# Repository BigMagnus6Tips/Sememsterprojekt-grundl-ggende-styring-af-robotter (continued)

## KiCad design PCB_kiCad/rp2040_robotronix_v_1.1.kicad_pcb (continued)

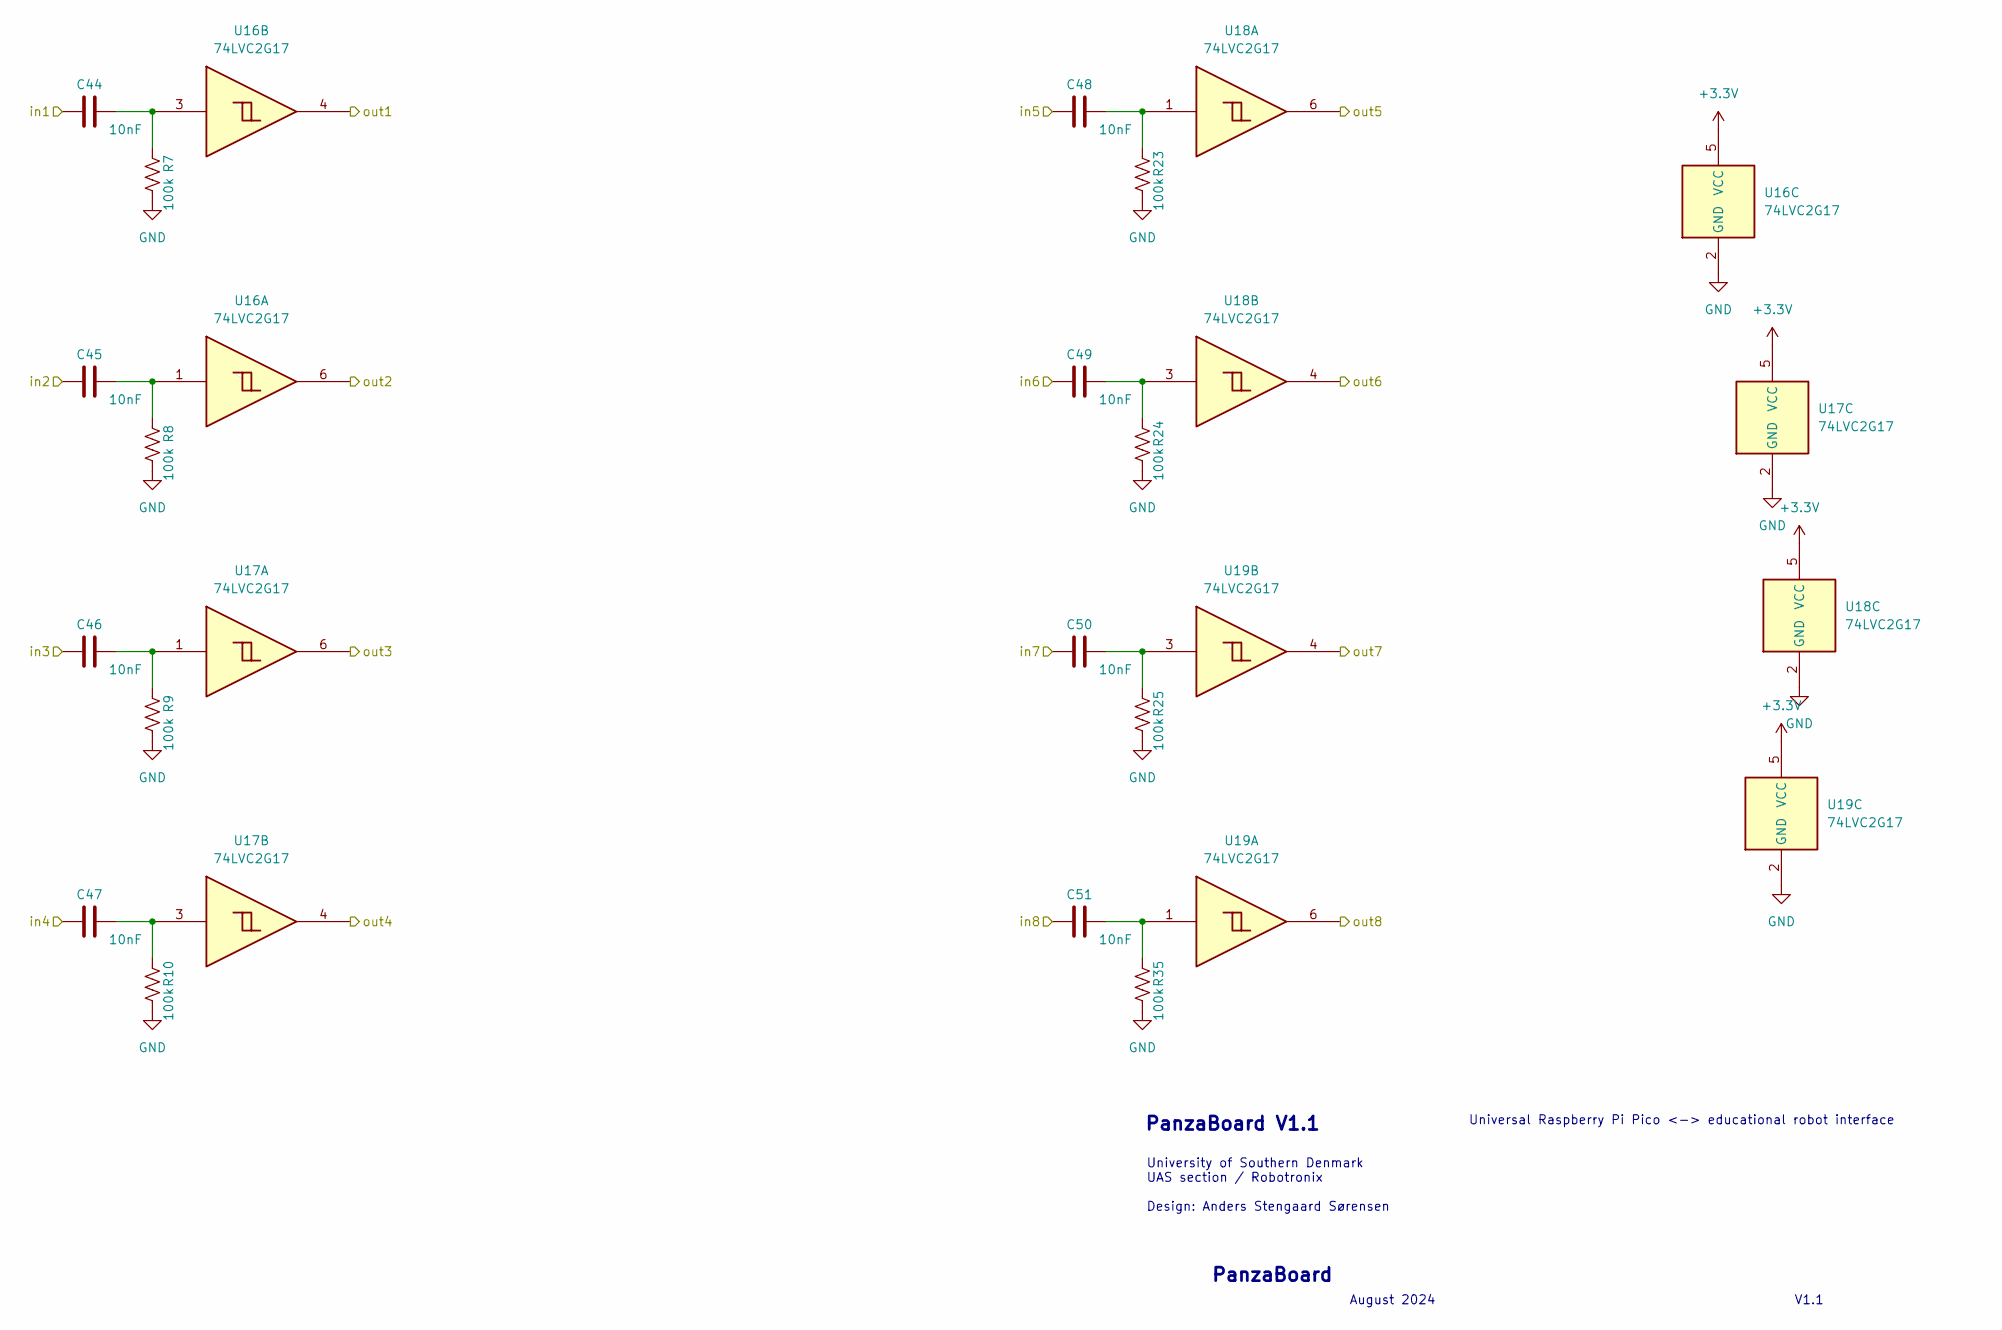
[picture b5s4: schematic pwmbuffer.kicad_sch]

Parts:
C44, C45, C46, C47, C48, C49, C50, C51: 10nF; C_0603_1608Metric
R7, R8, R9, R10, R23, R24, R25, R35: 100k; R_0603_1608Metric
U16, U17, U18, U19: 74LVC2G17; TSOP-6_1.65x3.05mm_P0.95mm

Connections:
/GP0: C44.2; also elsewhere on the board
/GP1: C45.2; also elsewhere on the board
/GP2: C46.2; also elsewhere on the board
/GP3: C47.2; also elsewhere on the board
/GP4: C48.2; also elsewhere on the board
/GP5: C49.2; also elsewhere on the board
/GP6: C50.2; also elsewhere on the board
/GP7: C51.2; also elsewhere on the board
/Motor drivers/PWM1: U16.4; also elsewhere on the board
/Motor drivers/PWM2: U16.6; also elsewhere on the board
/Motor drivers/PWM3: U17.6; also elsewhere on the board
/Motor drivers/PWM4: U17.4; also elsewhere on the board
/Motor drivers/PWM5: U18.6; also elsewhere on the board
/Motor drivers/PWM6: U18.4; also elsewhere on the board
/Motor drivers/PWM7: U19.4; also elsewhere on the board
/Motor drivers/PWM8: U19.6; also elsewhere on the board
GND: R7.2, R8.2, R9.2, R10.2, R23.2, R24.2, R25.2, R35.2, U16.2 (GND), U17.2 (GND), U18.2 (GND), U19.2 (GND); also elsewhere on the board
unnamed: C44.1, R7.1, U16.3
unnamed: C45.1, R8.1, U16.1
unnamed: C46.1, R9.1, U17.1
unnamed: C47.1, R10.1, U17.3
unnamed: C48.1, R23.1, U18.1
unnamed: C49.1, R24.1, U18.3
unnamed: C50.1, R25.1, U19.3
unnamed: C51.1, R35.1, U19.1
SD: U16.5 (VCC), U17.5 (VCC), U18.5 (VCC), U19.5 (VCC); also elsewhere on the board

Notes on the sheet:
Universal Raspberry Pi Pico <-> educational robot interface
August 2024
PanzaBoard V1.1
University of Southern Denmark UAS section / Robotronix Design: Anders Stengaard Sørensen
V1.1
PanzaBoard

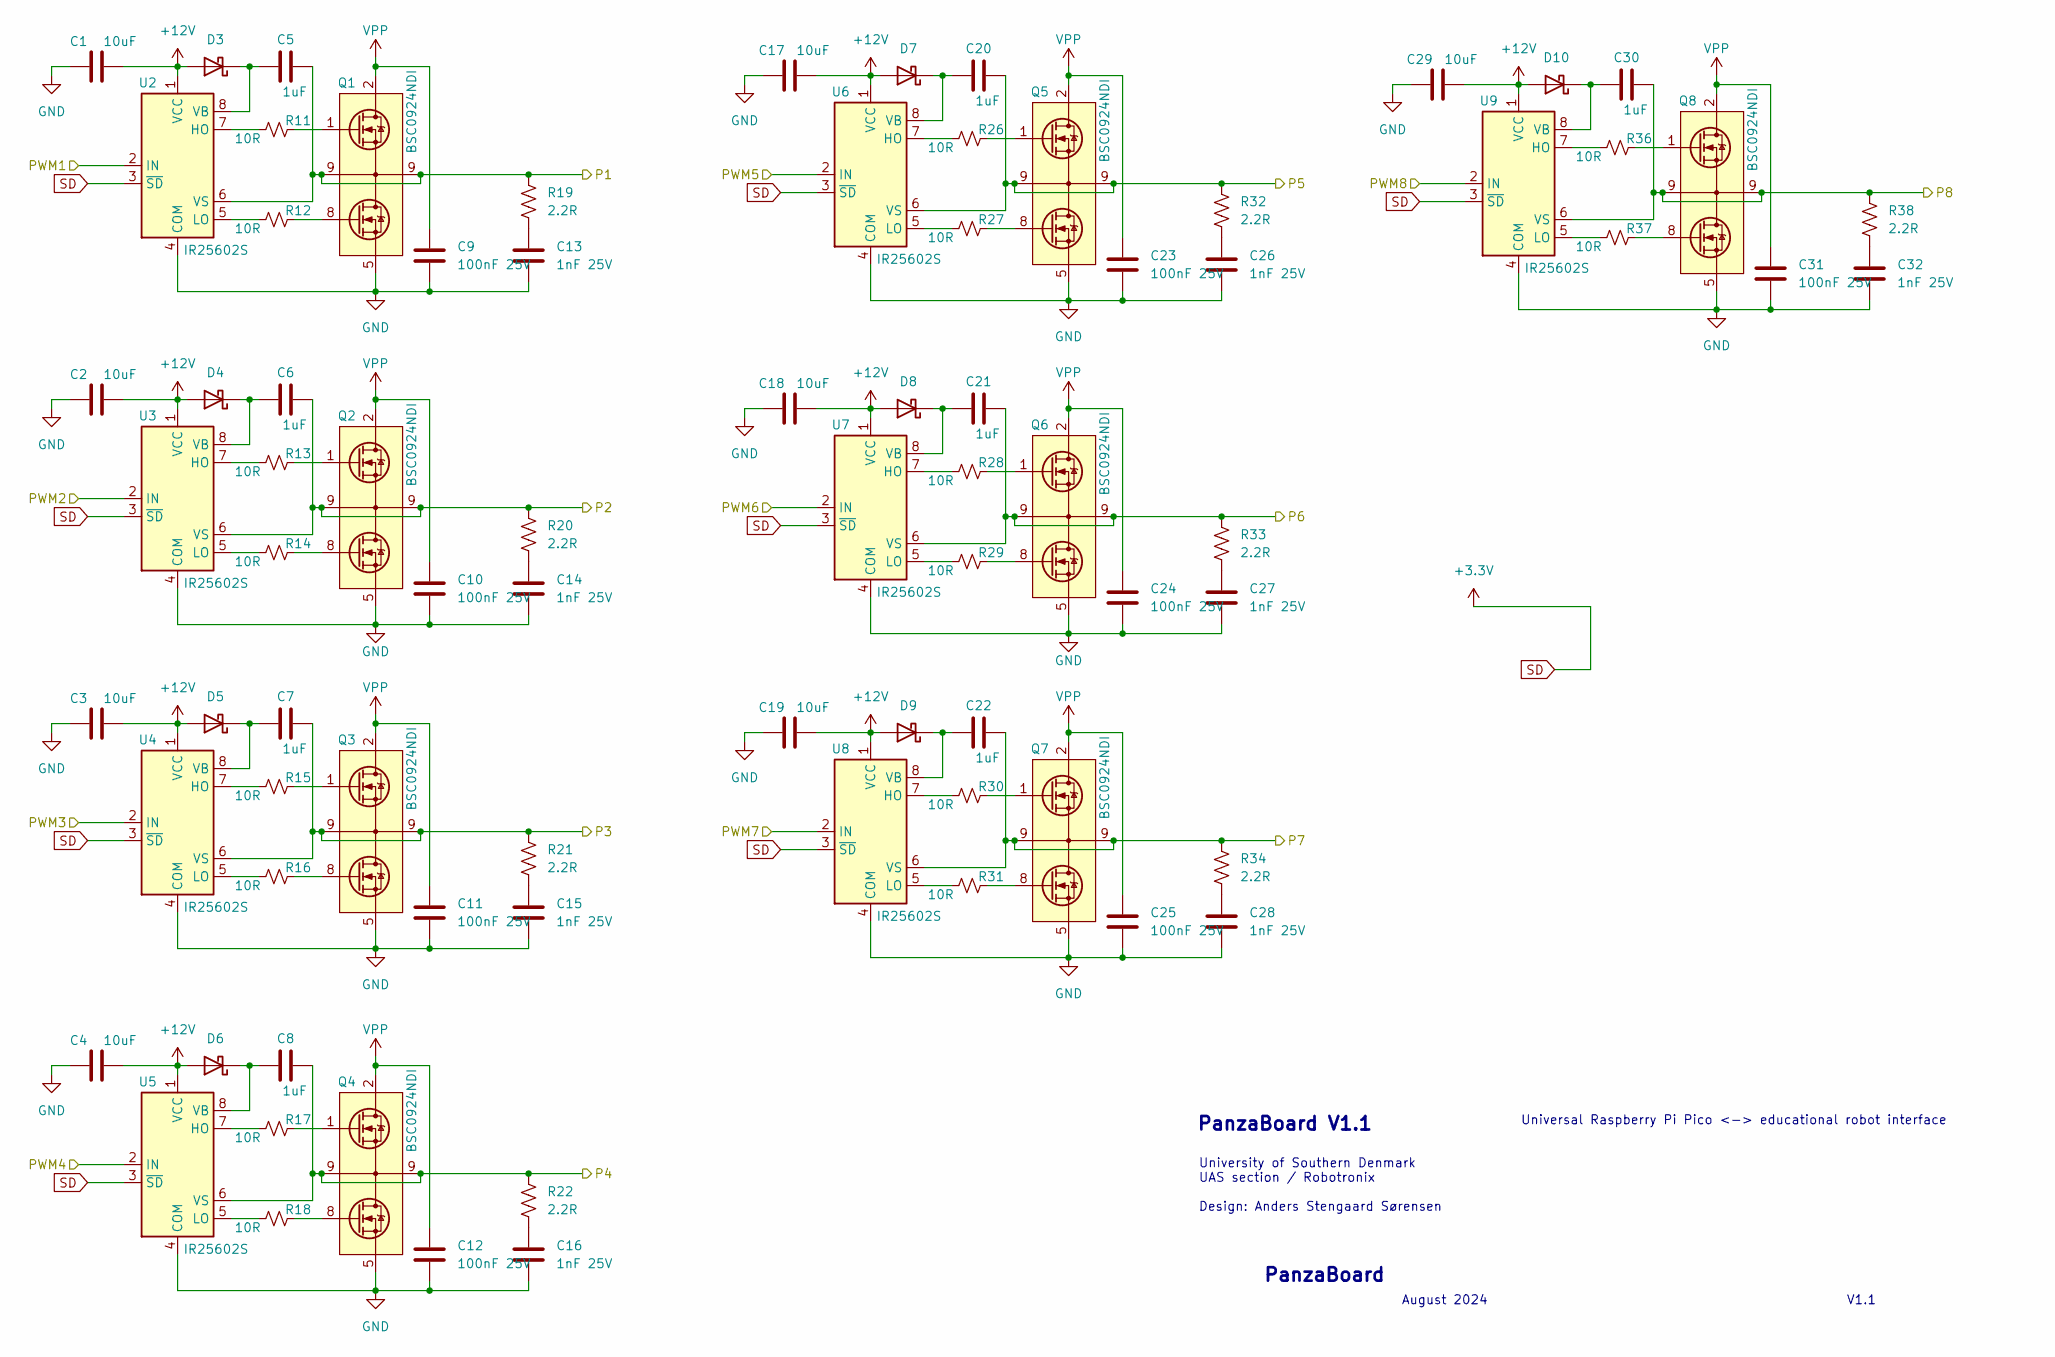
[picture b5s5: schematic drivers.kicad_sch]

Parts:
C1, C2, C3, C4, C17, C18, C19, C29: 10uF; C_1206_3216Metric; MFR# CL31A106KAHNFNE
C5, C6, C7, C8, C20, C21, C22, C30: 1uF; C_0603_1608Metric
C9, C10, C11, C12, C23, C24, C25, C31: 100nF 25V; C_0603_1608Metric
C13, C14, C15, C16, C26, C27, C28, C32: 1nF 25V; C_0603_1608Metric
D3, D4, D5, D6, D7, D8, D9, D10: CES521; D_SOD-523
Q1, Q2, Q3, Q4, Q5, Q6, Q7, Q8: BSC0924NDI; PG-TISON8; MFR# Infineon Technologies
R11, R12, R13, R14, R15, R16, R17, R18, R26, R27, R28, R29, R30, R31, R36, R37: 10R; R_0603_1608Metric
R19, R20, R21, R22, R32, R33, R34, R38: 2.2R; R_0603_1608Metric
U2, U3, U4, U5, U6, U7, U8, U9: IR25602S; SOIC-8_3.9x4.9mm_P1.27mm

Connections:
+12V: C1.2, C2.2, C3.2, C4.2, C17.2, C18.2, C19.2, C29.2, D3.2 (A), D4.2 (A), D5.2 (A), D6.2 (A), D7.2 (A), D8.2 (A), D9.2 (A), D10.2 (A), U2.1 (VCC), U3.1 (VCC), U4.1 (VCC), U5.1 (VCC), U6.1 (VCC), U7.1 (VCC), U8.1 (VCC), U9.1 (VCC); also elsewhere on the board
/Motor drivers/P1: C5.2, Q1.9, R19.1, U2.6 (VS); also elsewhere on the board
/Motor drivers/P2: C6.2, Q2.9, R20.1, U3.6 (VS); also elsewhere on the board
/Motor drivers/P3: C7.2, Q3.9, R21.1, U4.6 (VS); also elsewhere on the board
/Motor drivers/P4: C8.2, Q4.9, R22.1, U5.6 (VS); also elsewhere on the board
/Motor drivers/P5: C20.2, Q5.9, R32.1, U6.6 (VS); also elsewhere on the board
/Motor drivers/P6: C21.2, Q6.9, R33.1, U7.6 (VS); also elsewhere on the board
/Motor drivers/P7: C22.2, Q7.9, R34.1, U8.6 (VS); also elsewhere on the board
/Motor drivers/P8: C30.2, Q8.9, R38.1, U9.6 (VS); also elsewhere on the board
/Motor drivers/PWM1: U2.2 (IN); also elsewhere on the board
/Motor drivers/PWM2: U3.2 (IN); also elsewhere on the board
/Motor drivers/PWM3: U4.2 (IN); also elsewhere on the board
/Motor drivers/PWM4: U5.2 (IN); also elsewhere on the board
/Motor drivers/PWM5: U6.2 (IN); also elsewhere on the board
/Motor drivers/PWM6: U7.2 (IN); also elsewhere on the board
/Motor drivers/PWM7: U8.2 (IN); also elsewhere on the board
/Motor drivers/PWM8: U9.2 (IN); also elsewhere on the board
GND: C1.1, C2.1, C3.1, C4.1, C9.1, C10.1, C11.1, C12.1, C13.1, C14.1, C15.1, C16.1, C17.1, C18.1, C19.1, C23.1, C24.1, C25.1, C26.1, C27.1, C28.1, C29.1, C31.1, C32.1, Q1.5, Q1.6, Q1.7, Q2.5, Q2.6, Q2.7, Q3.5, Q3.6, Q3.7, Q4.5, Q4.6, Q4.7, Q5.5, Q5.6, Q5.7, Q6.5, Q6.6, Q6.7, Q7.5, Q7.6, Q7.7, Q8.5, Q8.6, Q8.7, U2.4 (COM), U3.4 (COM), U4.4 (COM), U5.4 (COM), U6.4 (COM), U7.4 (COM), U8.4 (COM), U9.4 (COM); also elsewhere on the board
unnamed: C13.2, R19.2
unnamed: C14.2, R20.2
unnamed: C15.2, R21.2
unnamed: C16.2, R22.2
unnamed: C26.2, R32.2
unnamed: C27.2, R33.2
unnamed: C28.2, R34.2
unnamed: C32.2, R38.2
unnamed: C5.1, D3.1 (K), U2.8 (VB)
unnamed: C6.1, D4.1 (K), U3.8 (VB)
unnamed: C7.1, D5.1 (K), U4.8 (VB)
unnamed: C8.1, D6.1 (K), U5.8 (VB)
unnamed: C20.1, D7.1 (K), U6.8 (VB)
unnamed: C21.1, D8.1 (K), U7.8 (VB)
unnamed: C22.1, D9.1 (K), U8.8 (VB)
unnamed: C30.1, D10.1 (K), U9.8 (VB)
unnamed: Q1.1, R11.2
unnamed: Q1.8, R12.2
unnamed: Q2.1, R13.2
unnamed: Q2.8, R14.2
unnamed: Q3.1, R15.2
unnamed: Q3.8, R16.2
unnamed: Q4.1, R17.2
unnamed: Q4.8, R18.2
unnamed: Q5.1, R26.2
unnamed: Q5.8, R27.2
unnamed: Q6.1, R28.2
unnamed: Q6.8, R29.2
unnamed: Q7.1, R30.2
unnamed: Q7.8, R31.2
unnamed: Q8.1, R36.2
unnamed: Q8.8, R37.2
unnamed: R11.1, U2.7 (HO)
unnamed: R12.1, U2.5 (LO)
unnamed: R13.1, U3.7 (HO)
unnamed: R14.1, U3.5 (LO)
unnamed: R15.1, U4.7 (HO)
unnamed: R16.1, U4.5 (LO)
unnamed: R17.1, U5.7 (HO)
unnamed: R18.1, U5.5 (LO)
unnamed: R26.1, U6.7 (HO)
unnamed: R27.1, U6.5 (LO)
unnamed: R28.1, U7.7 (HO)
unnamed: R29.1, U7.5 (LO)
unnamed: R30.1, U8.7 (HO)
unnamed: R31.1, U8.5 (LO)
unnamed: R36.1, U9.7 (HO)
unnamed: R37.1, U9.5 (LO)
SD: U2.3 (~SD), U3.3 (~SD), U4.3 (~SD), U5.3 (~SD), U6.3 (~SD), U7.3 (~SD), U8.3 (~SD), U9.3 (~SD); also elsewhere on the board
VPP: C9.2, C10.2, C11.2, C12.2, C23.2, C24.2, C25.2, C31.2, Q1.2, Q1.3, Q1.4, Q2.2, Q2.3, Q2.4, Q3.2, Q3.3, Q3.4, Q4.2, Q4.3, Q4.4, Q5.2, Q5.3, Q5.4, Q6.2, Q6.3, Q6.4, Q7.2, Q7.3, Q7.4, Q8.2, Q8.3, Q8.4; also elsewhere on the board

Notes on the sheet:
PanzaBoard
University of Southern Denmark UAS section / Robotronix Design: Anders Stengaard Sørensen
V1.1
August 2024
Universal Raspberry Pi Pico <-> educational robot interface
PanzaBoard V1.1

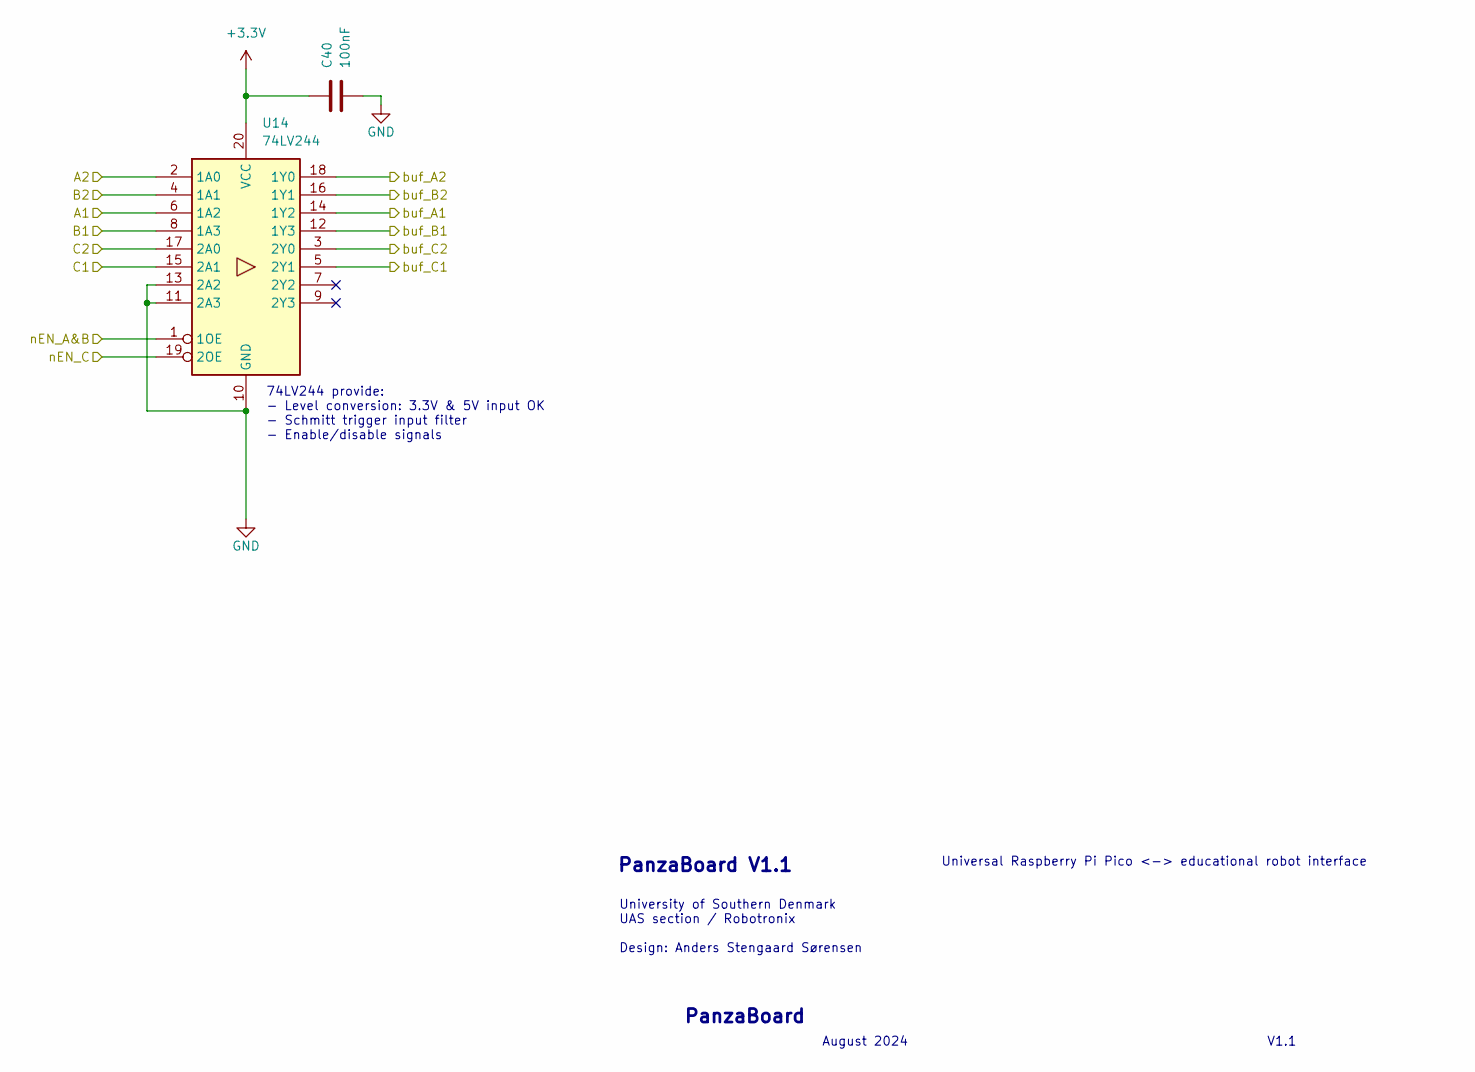
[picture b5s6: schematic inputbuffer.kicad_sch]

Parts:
C40: 100nF; C_0603_1608Metric
U14: 74LV244; TSSOP-20_4.4x6.5mm_P0.65mm; MFR# Nexperia

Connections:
/GP8: U14.5 (2Y1); also elsewhere on the board
/GP9: U14.3 (2Y0); also elsewhere on the board
/GP12: U14.12 (1Y3); also elsewhere on the board
/GP13: U14.14 (1Y2); also elsewhere on the board
/GP14: U14.16 (1Y1); also elsewhere on the board
/GP15: U14.18 (1Y0); also elsewhere on the board
/Input buffer/A1: U14.6 (1A2); also elsewhere on the board
/Input buffer/A2: U14.2 (1A0); also elsewhere on the board
/Input buffer/B1: U14.8 (1A3); also elsewhere on the board
/Input buffer/B2: U14.4 (1A1); also elsewhere on the board
/Input buffer/C1: U14.15 (2A1); also elsewhere on the board
/Input buffer/C2: U14.17 (2A0); also elsewhere on the board
/Input buffer/nEN_A&B: U14.1 (1OE); also elsewhere on the board
/Input buffer/nEN_C: U14.19 (2OE); also elsewhere on the board
GND: C40.1, U14.10 (GND), U14.11 (2A3), U14.13 (2A2); also elsewhere on the board
SD: C40.2, U14.20 (VCC); also elsewhere on the board

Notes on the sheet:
University of Southern Denmark UAS section / Robotronix Design: Anders Stengaard Sørensen
PanzaBoard V1.1
Universal Raspberry Pi Pico <-> educational robot interface
74LV244 provide: - Level conversion: 3.3V & 5V input OK - Schmitt trigger input filter - Enable/disable signals
August 2024
V1.1
PanzaBoard

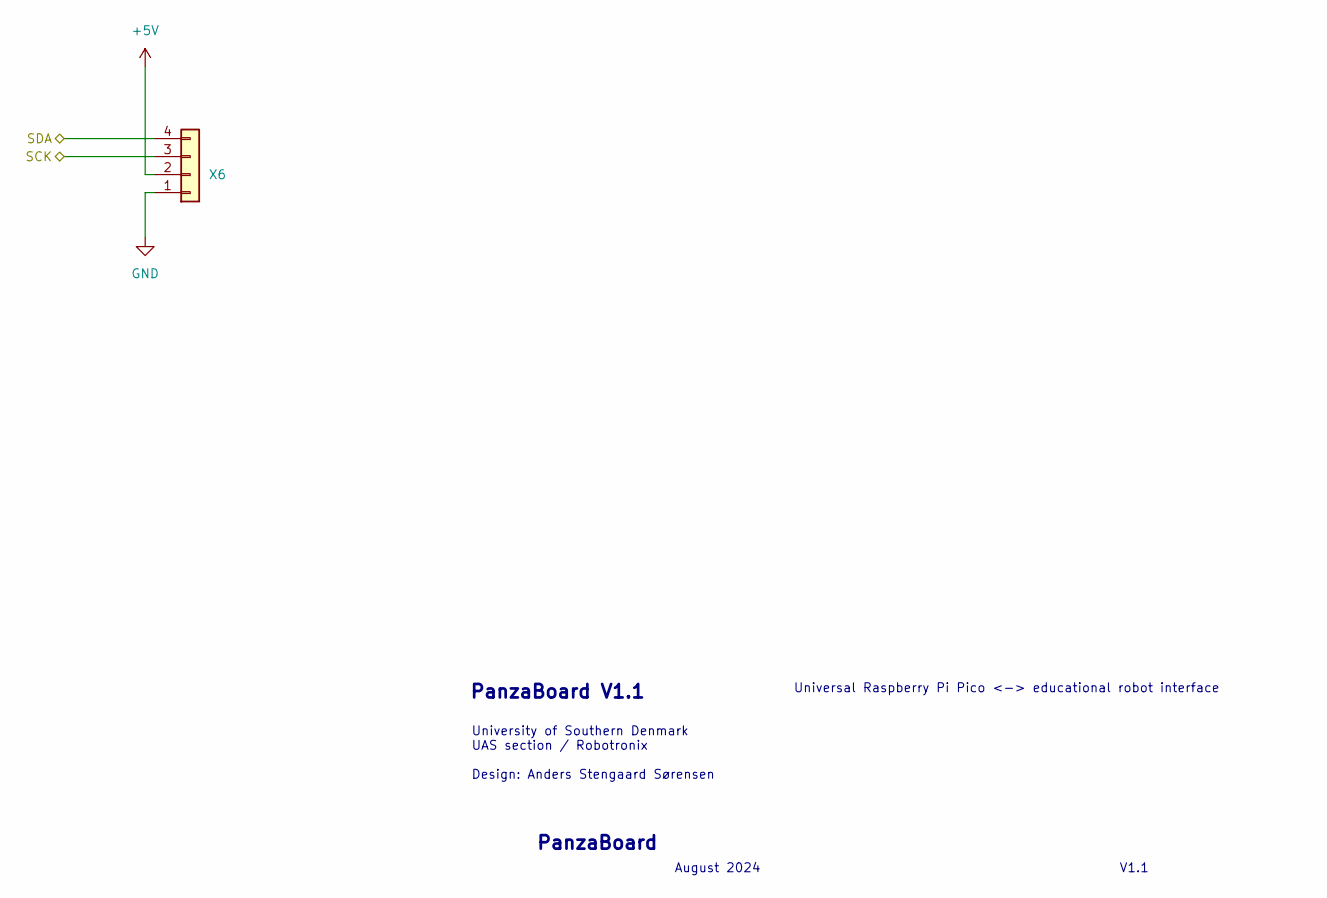
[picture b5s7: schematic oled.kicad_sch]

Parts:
X6: Conn_01x04; Molex_KK-254_AE-6410-04A_1x04_P2.54mm_Vertical

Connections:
+5V: X6.2; also elsewhere on the board
/GP20: X6.4; also elsewhere on the board
/GP21: X6.3; also elsewhere on the board
GND: X6.1; also elsewhere on the board

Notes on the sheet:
Universal Raspberry Pi Pico <-> educational robot interface
PanzaBoard V1.1
August 2024
PanzaBoard
V1.1
University of Southern Denmark UAS section / Robotronix Design: Anders Stengaard Sørensen

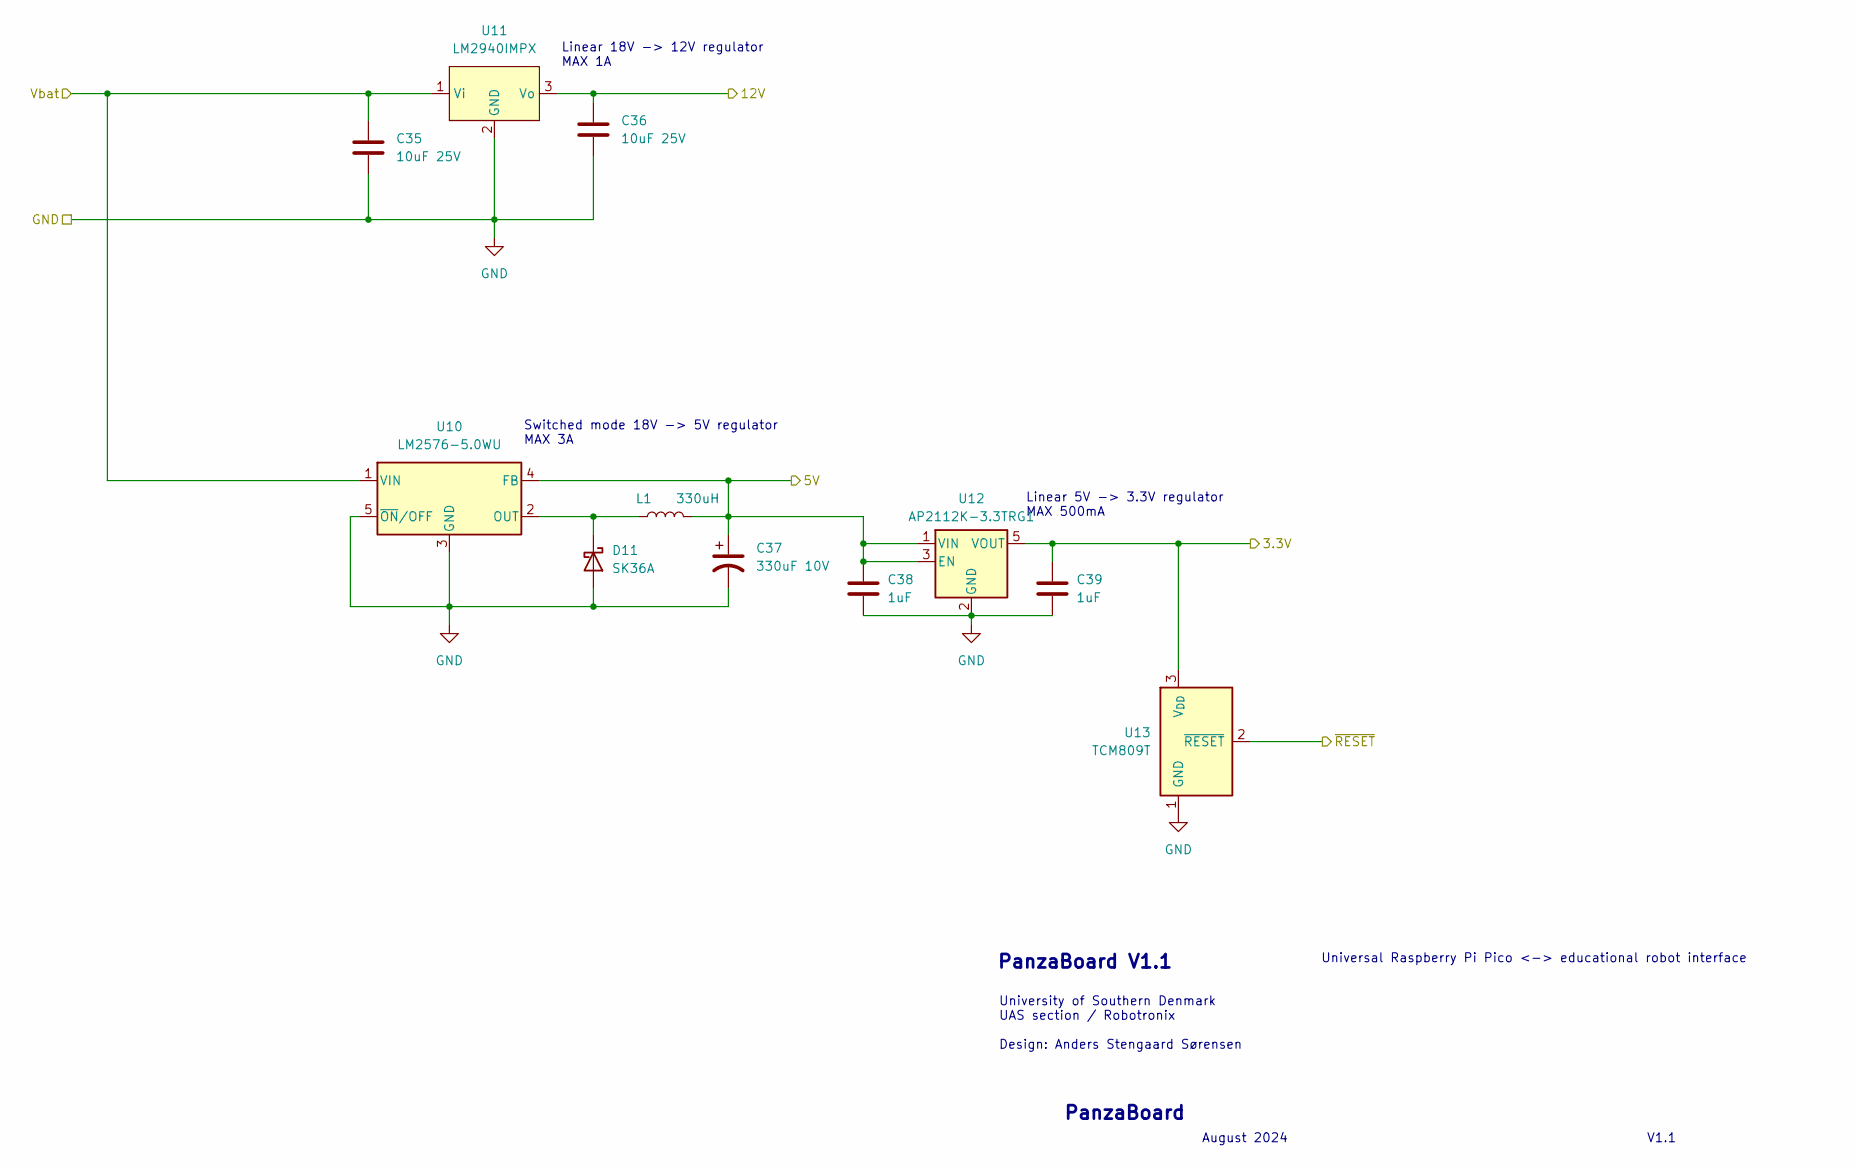
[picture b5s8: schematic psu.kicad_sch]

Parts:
C35, C36: 10uF 25V; C_1206_3216Metric; MFR# CL31A106KAHNFNE
C37: 330uF 10V; CP_Radial_D10.0mm_P5.00mm; MFR# Wurth Elektronik
C38, C39: 1uF; C_1206_3216Metric; MFR# CC0603KPX5R8BB105
D11: SK36A; D_SMA; MFR# Micro Commercial Components (MCC)
L1: 330uH; L_Murata_6000B; MFR# Murata Power Solutions
U10: LM2576-5.0WU; TO-263-5_TabPin3; MFR# Microchip Technology
U11: LM2940IMPX; SOT-223-3_TabPin2
U12: AP2112K-3.3TRG1; SOT-23-5; MFR# Diodes Incorporated
U13: TCM809T; SOT-323_SC-70; MFR# Microchip Technology

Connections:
+5V: C37.1, C38.1, L1.2, U10.4 (FB), U12.1 (VIN), U12.3 (EN); also elsewhere on the board
+12V: C36.1, U11.3 (Vo); also elsewhere on the board
/RUN: U13.2 (~RESET); also elsewhere on the board
GND: C35.2, C36.2, C37.2, C38.2, C39.2, D11.2 (A), U10.3 (GND), U10.5 (~ON/OFF), U11.2 (GND), U12.2 (GND), U13.1 (GND); also elsewhere on the board
unnamed: D11.1 (K), L1.1, U10.2 (OUT)
SD: C39.1, U12.5 (VOUT), U13.3 (V_{DD}); also elsewhere on the board
Vbat: C35.1, U10.1 (VIN), U11.1 (Vi); also elsewhere on the board

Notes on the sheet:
Linear 5V -> 3.3V regulator MAX 500mA
August 2024
University of Southern Denmark UAS section / Robotronix Design: Anders Stengaard Sørensen
Universal Raspberry Pi Pico <-> educational robot interface
Linear 18V -> 12V regulator MAX 1A
PanzaBoard V1.1
Switched mode 18V -> 5V regulator MAX 3A
PanzaBoard
V1.1

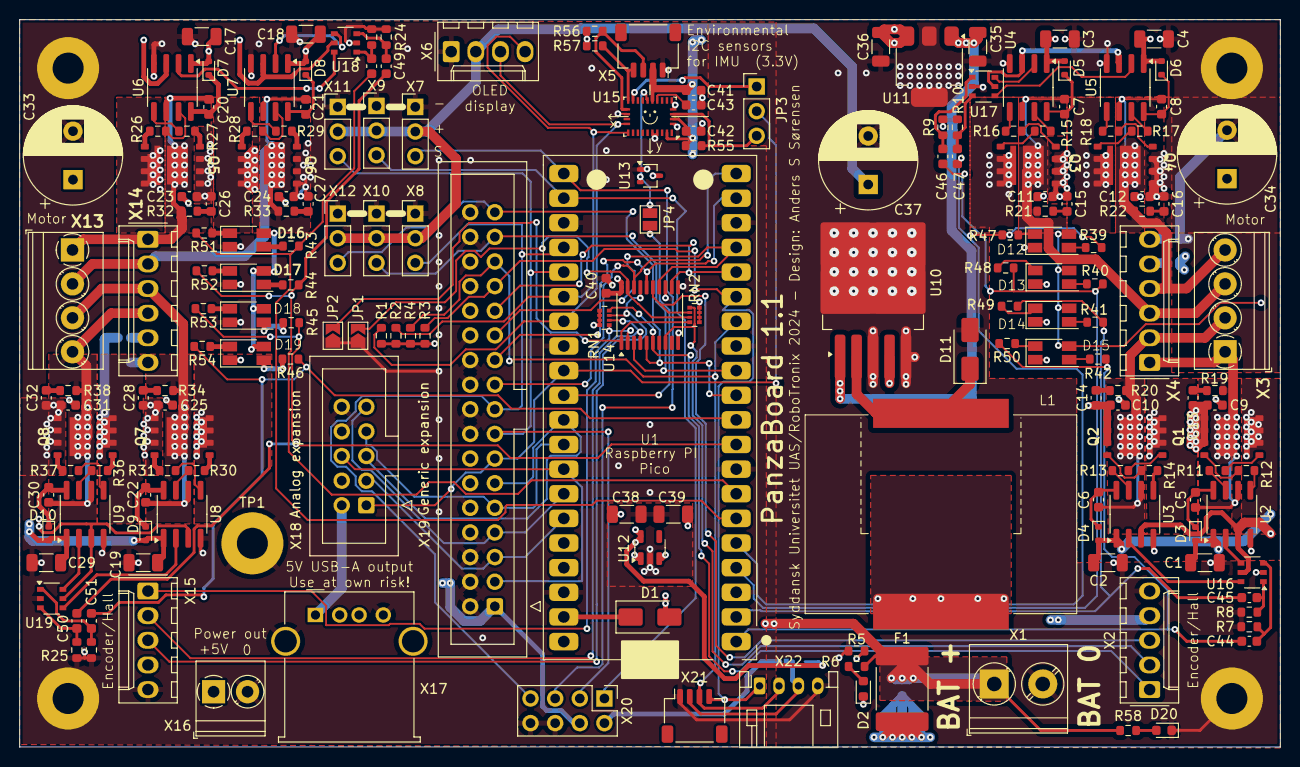
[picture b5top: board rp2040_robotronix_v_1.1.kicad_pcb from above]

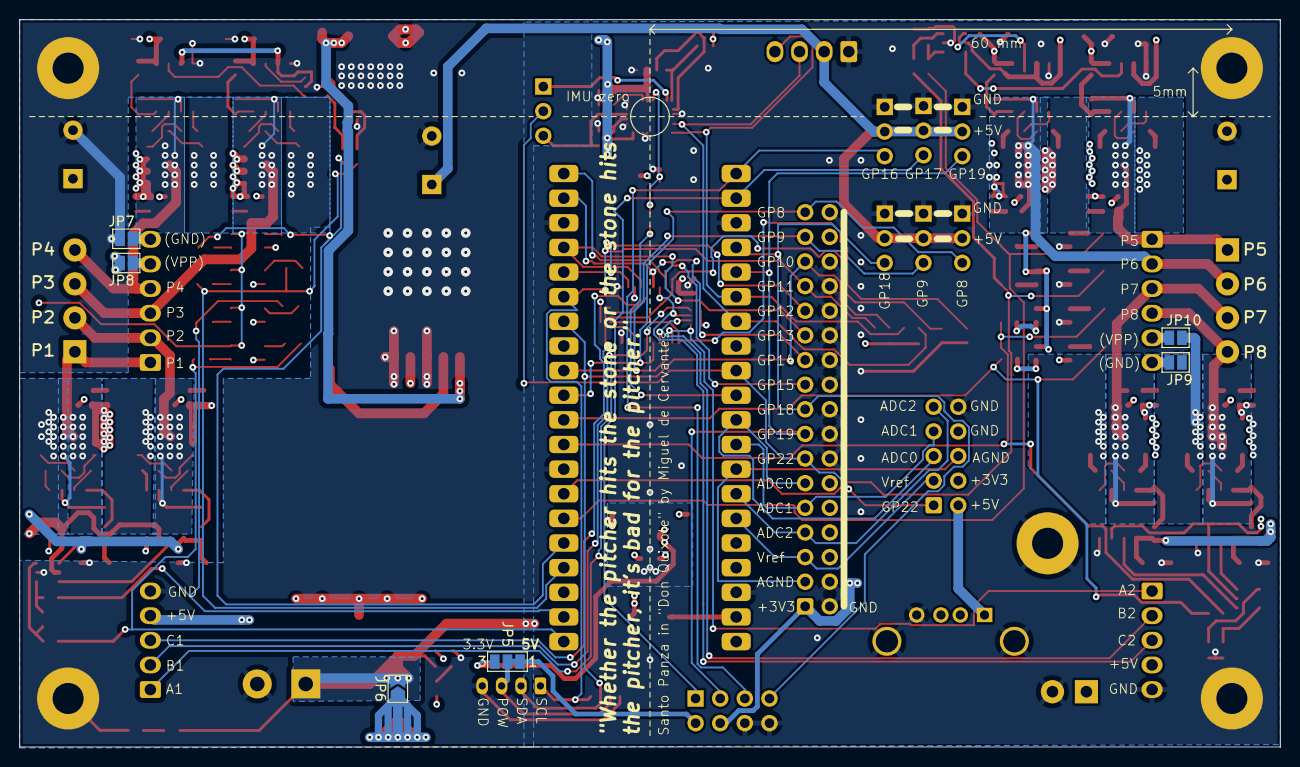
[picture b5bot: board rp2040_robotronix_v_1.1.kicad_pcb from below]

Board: 4 copper layers, 130.0 x 75.0 mm, 197 parts (6 on the bottom side), 146 nets.

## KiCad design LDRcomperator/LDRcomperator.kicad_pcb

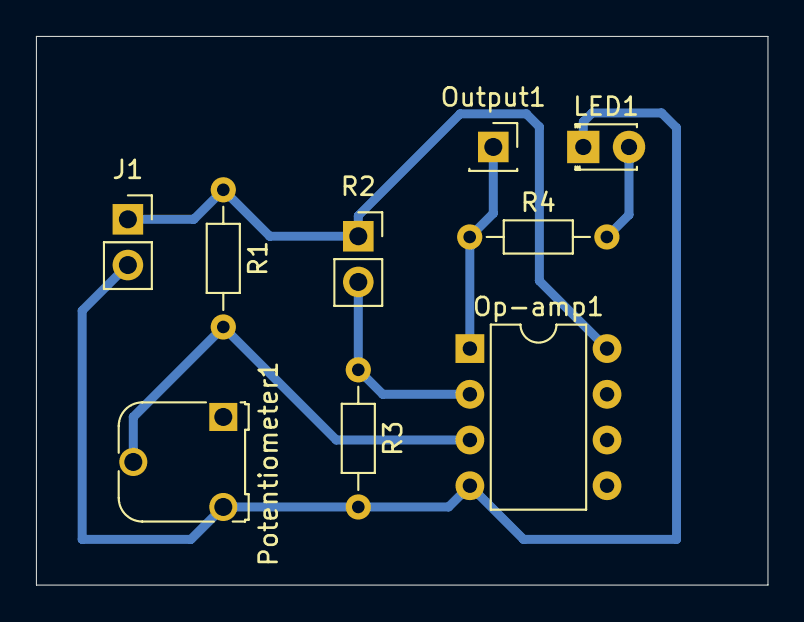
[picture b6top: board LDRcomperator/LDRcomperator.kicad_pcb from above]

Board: 2 copper layers, 40.6 x 30.5 mm, 9 parts (0 on the bottom side), 6 nets.

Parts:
J1: Screw_Terminal_01x02; PinSocket_1x02_P2.54mm_Vertical
LED1: LED; LED_D1.8mm_W3.3mm_H2.4mm
Op-amp1: MCP6001R; DIP-8_W7.62mm
Output1: Conn_01x01_MountingPin; PinSocket_1x01_P2.54mm_Vertical
Potentiometer1: 10k ohm; Potentiometer_Runtron_RM-065_Vertical
R1: 2.2k; R_Axial_DIN0204_L3.6mm_D1.6mm_P7.62mm_Horizontal
R2: LDR03; PinSocket_1x02_P2.54mm_Vertical
R3: 2,2k ohm; R_Axial_DIN0204_L3.6mm_D1.6mm_P7.62mm_Horizontal
R4: 65 ohm; R_Axial_DIN0204_L3.6mm_D1.6mm_P7.62mm_Horizontal

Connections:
+3V3: J1.1, Op-amp1.8 (V+), R1.1, R2.1
GND: J1.2, LED1.1 (K), Op-amp1.4 (V-), Potentiometer1.3, R3.2
unnamed: LED1.2 (A), R4.2
unnamed: Op-amp1.3 (+), Potentiometer1.2, R1.2
unnamed: Op-amp1.2 (-), R2.2, R3.1
unnamed: Op-amp1.1, Output1.1, R4.1

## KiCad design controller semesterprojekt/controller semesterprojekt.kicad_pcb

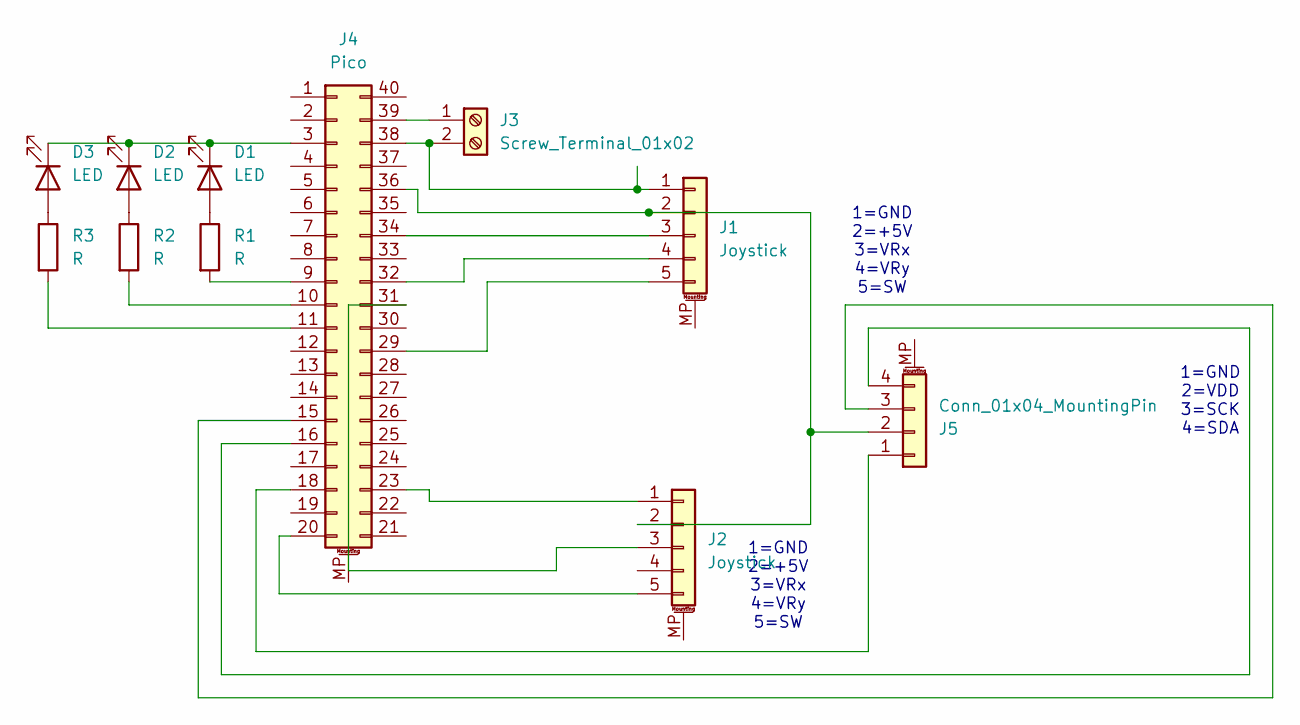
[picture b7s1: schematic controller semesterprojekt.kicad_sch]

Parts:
D1, D2, D3: LED; LED_D3.0mm
J1, J2: Joystick; PinSocket_1x05_P2.54mm_Vertical
J3: Screw_Terminal_01x02; TerminalBlock_Phoenix_MKDS-1,5-2-5.08_1x02_P5.08mm_Horizont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
J4: Pico; RP_pico
J5: Conn_01x04_MountingPin; PinSocket_1x04_P2.54mm_Vertical
R1, R2, R3: R; R_Axial_DIN0309_L9.0mm_D3.2mm_P15.24mm_Horizontal

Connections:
unnamed: D1.2 (A), R1.1
unnamed: D1.1 (K), D2.1 (K), D3.1 (K), J4.3
unnamed: D2.2 (A), R2.1
unnamed: D3.2 (A), R3.1
unnamed: J1.1, J3.2, J4.38
unnamed: J1.2, J2.2, J4.36, J5.2
unnamed: J1.3, J4.34
unnamed: J1.4, J4.32
unnamed: J1.5, J4.29
unnamed: J2.1, J4.23
unnamed: J2.3, J4.31
unnamed: J2.5, J4.20
unnamed: J3.1, J4.39
unnamed: J4.9, R1.2
unnamed: J4.10, R2.2
unnamed: J4.11, R3.2
unnamed: J4.15, J5.3
unnamed: J4.16, J5.4
unnamed: J4.18, J5.1

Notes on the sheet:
1=GND 2=VDD 3=SCK 4=SDA
1=GND 2=+5V 3=VRx 4=VRy 5=SW

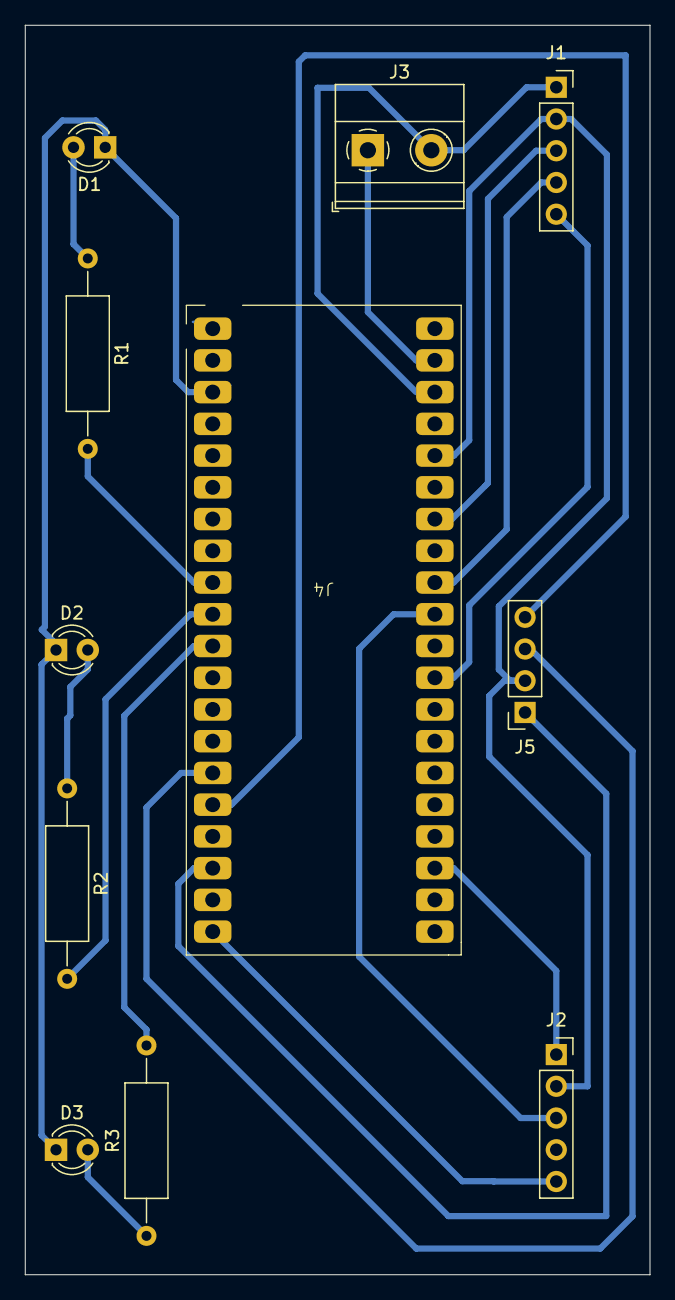
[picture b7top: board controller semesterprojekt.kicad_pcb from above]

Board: 2 copper layers, 50.0 x 100.0 mm, 11 parts (0 on the bottom side), 19 nets.

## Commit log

2024-11-06 Initializing repo
2024-11-06 test
2024-11-06 Opgave 2.3ish
2024-11-06 Feardig onsdag 6-11
2024-11-06 Deleted unused code
2024-11-11 test2
2024-11-11 Billede 1.1
2024-11-11 LED/LDR hardware integration
2024-11-11 Indsat billeder og source code
2024-11-11 Portfolio_edits
2024-11-11 Indsat source code
2024-11-11 Grafer
2024-11-11 Video og billeder
2024-11-11 reference to 2.2
2024-11-13 Joystick_test
2024-11-15 notebook færdig
2024-11-15 ryddet lidt op
2024-11-15 flowchart opdatering i bunden
2024-11-16 joystick improvement
2024-11-17 small changes
2024-11-17 ny flowchart
2024-11-17 threshold added to notebook
2024-11-17 ryddet meget op og tror nok det er godt nok
2024-11-17 Portfølje 3 aflevering
2024-11-17 no clue
2024-11-18 opdaterede metodeovervejelser 1
2024-11-18 new dataplots
2024-11-18 added client code
2024-11-18 added server code
2024-11-18 Deadzone Variable introduced and set to 0.1 for improvement of the controller deadzone.
2024-11-18 Made classes for Wifi but not sure if it works
2024-11-18 KillSwitch implemented
2024-11-18 portfolie 3 fil til at beholde den kode, før vi har kodet for meget videre.
2024-11-18 pcb images
2024-11-20 cleaned up the classes
2024-11-20 readded killswitch after merge
2024-11-20 bug fix...
2024-11-20 idk new commit
2024-11-22 ryddet op i folderne
2024-11-22 added kicad files including controller
2024-11-25 added comms for communikation
2024-11-25 imporoved comms
2024-11-25 Updated kiCad
2024-11-25 Updated kicad_pcb
2024-11-27 implemented joystick class to wificlient
2024-11-27 wifi and joystick updates
2024-11-27 renammed a function
2024-11-27 renammed again
2024-11-27 renammed again again
2024-11-27 added BLE and joystick tester
2024-11-28 OLED og Kicad for elektromagnet og LDR boards
2024-11-28 updated joystick to include button
2024-11-28 controller update
2024-11-28 made it work wireless with bluetooth
2024-11-28 button added
2024-11-28 something to do with the OLED screen
2024-11-28 minor changes to oled test
2024-11-28 display done
2024-11-29 Made shit work
2024-11-29 more codes transfered to pf4
2024-12-01 Joystick readability improved
2024-12-01 added comments
2024-12-01 updated comments to have the same language and case
2024-12-02 spellcheck
2024-12-02 Fire Mcking beginning
2024-12-02 RobotClasses imported to Fire Mcking
2024-12-02 Mcking kode iteration 1
2024-12-05 Alex portfolie 3
2024-12-05 added updated picture
2024-12-05 added image
2024-12-05 Portfolie 3 changes
2024-12-05 whatever
2024-12-05 minor changes
2024-12-05 portfolie 3 fix
2024-12-05 portfolio 3 fixes
2024-12-12 made things to portfolio 3
2024-12-12 New portfolio 3 completely finished
2024-12-12 changes to humle
2024-12-12 fire mcking upgrades
2024-12-12 More humle dead reckoning
2024-12-12 added kicad to comparator
2024-12-12 added interrupt for firemacking
2024-12-12 ik rigtig noget
2024-12-13 modified kicad for LDR
2024-12-13 Added test for homing function
2024-12-15 updated the LDRComperator kicad drawing
2024-12-15 added karsl crane -Lukas
2024-12-15 modified Karls crane code
2024-12-15 kicad improvments for ldrCompartor
2024-12-15 added second LDR and made it work
2024-12-15 mindre ændringer til humle samt legacy kode fra pf2
2024-12-16 made speed for firemcking
2024-12-16 Kran
2024-12-16 ændringer til coordinatesplotter
2024-12-16 uploaded PCB kicad filer
2024-12-16 pick up bolt function
2024-12-16 added kicad flip flop thing
2024-12-16 made flip flop work
2024-12-16 Elektromagnet kicad
2024-12-16 Kicad 2
2024-12-16 added bolt coords
2024-12-17 ny lightning mcqueen kode med flip flop
2024-12-17 did something with kicad idk
2024-12-17 commit for mcking trying using flip flop
2024-12-17 Uploaded old fast mcking
2024-12-17 major changes
2024-12-17 Crane tweaks
2024-12-17 almost safe fire mcking
2024-12-17 McKing smooth speed at 800
2024-12-17 smooth 750 speed fire mcking
2024-12-18 ultra optimized code (experimental)
2025-01-04 Drag race
2025-01-04 random
2025-01-04 Karls ændringer
2025-01-06 KiCad changes
2025-01-06 kicad stuuf idk
2025-01-07 Fraud
2025-01-19 Rapporten
2025-01-19 Powerpoint
2025-01-23 Bare haft kigget på KiCad tegningerne
2025-01-26 Added much needed comments for the controller
2025-01-26 PF4 PP
2025-01-26 idk what to write
